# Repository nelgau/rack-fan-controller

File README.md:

# Rack Hardware Projects

Collection of hardware projects for a Penn Elcom server enclosure

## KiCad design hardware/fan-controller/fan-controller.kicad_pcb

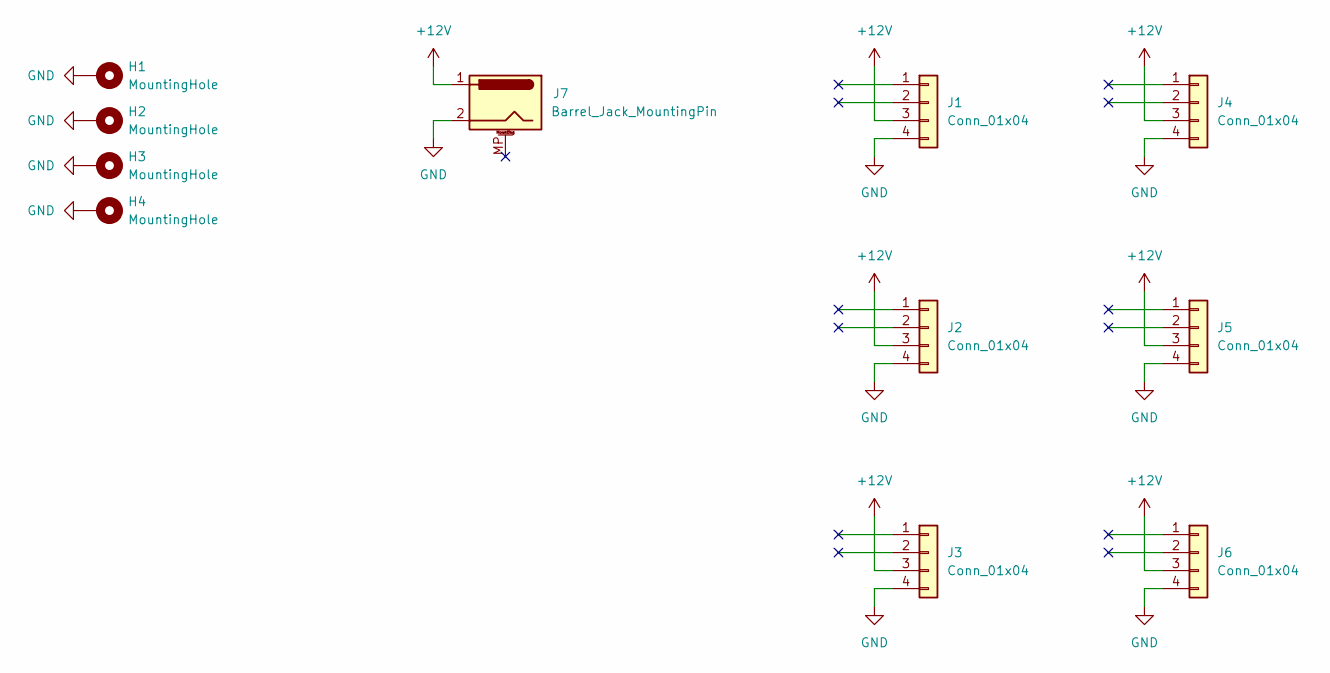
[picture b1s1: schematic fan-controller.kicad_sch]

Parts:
H1, H2, H3, H4: MountingHole; MountingHole_3.2mm_M3_Pad
J1, J2, J3, J4, J5, J6: Conn_01x04; PinHeader_1x04_P2.54mm_Horizontal
J7: Barrel_Jack_MountingPin; BarrelJack_CUI_PJ-063AH_Horizontal

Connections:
+12V: J1.3, J2.3, J3.3, J4.3, J5.3, J6.3, J7.1
GND: H1.1, H2.1, H3.1, H4.1, J1.4, J2.4, J3.4, J4.4, J5.4, J6.4, J7.2

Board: 2 copper layers, 11 parts (0 on the bottom side), 2 nets, no tracks yet.

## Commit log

2024-03-21 Create Kicad project
2024-03-21 Add .gitignore for Kicad
2024-03-22 Basic fan controller as distro board
2024-03-22 Fabrication outputs for revA
2024-04-11 Add personal KiCad library as submodule
2024-04-13 Create project for USB redriver
2024-04-14 Initial schematic for USB redriver
    This schematic is copied from a USB 3.0 redriver cable from Amazon.
2024-04-15 Assign part numbers and footprints to USB connectors
2024-04-16 Use local USB connector footprints to pair with 3D models
2024-04-22 Transfer values for capacitors
2024-04-23 Transfer values for resistors
2024-04-24 Assign footprints for resistors
